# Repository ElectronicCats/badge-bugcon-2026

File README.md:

# Badge BugCON 2026 · Guía de uso

¡Bienvenida, bienvenido a **BugCON 2026**! Esta guía te explica, paso a paso,
cómo usar tu Badge. No necesitas saber de electrónica ni de programación.

## ¿Qué es el Badge?

El Badge es tu gafete electrónico del evento. Diseñado por Electronic Cats
para BugCON 2026, tiene un tema de fútbol: la **Copa BugCon 2026**. Con él
puedes:

- Mostrar tu **estampa**: una tarjeta de jugador con tu apodo, tu villa y tus
  estadísticas.
- **Intercambiar estampas** con otros asistentes y llenar tu **álbum**.
- Jugar **Penales**, la **Copa BugCon** y **Futbolito**.
- Usar herramientas: reloj, temporizador, luz, agenda del evento y control
  remoto para TV.
- Configurarlo desde tu computadora con el [configurador web](#configurador-web):
  una página para tu estampa, tu avatar, tus imágenes y tu álbum.
- Ir más allá con las [herramientas de computadora](tools/README.md).

## Contenido

- [Badge BugCON 2026 · Guía de uso](#badge-bugcon-2026--guía-de-uso)
  - [¿Qué es el Badge?](#qué-es-el-badge)
  - [Contenido](#contenido)
  - [Conoce tu Badge](#conoce-tu-badge)
  - [Encender y apagar](#encender-y-apagar)
    - [Encender](#encender)
    - [Apagar](#apagar)
    - [Reposo automático](#reposo-automático)
  - [Tu primer encendido](#tu-primer-encendido)
  - [Cómo moverte por el Badge](#cómo-moverte-por-el-badge)
  - [El gafete: la pantalla principal](#el-gafete-la-pantalla-principal)
    - [La barra de arriba](#la-barra-de-arriba)
  - [El menú](#el-menú)
  - [Mi Estampa: personaliza tu tarjeta](#mi-estampa-personaliza-tu-tarjeta)
    - [Nickname (tu apodo)](#nickname-tu-apodo)
    - [Villa](#villa)
    - [Posición](#posición)
    - [Estadísticas](#estadísticas)
    - [Desde el teléfono](#desde-el-teléfono)
  - [Intercambiar estampas](#intercambiar-estampas)
    - [Paso a paso](#paso-a-paso)
    - [Qué significa cada resultado](#qué-significa-cada-resultado)
    - [Recibir sin presionar nada](#recibir-sin-presionar-nada)
    - [Visitar las villas](#visitar-las-villas)
    - [Tu privacidad](#tu-privacidad)
  - [El Álbum](#el-álbum)
    - [La portada](#la-portada)
    - [Las páginas](#las-páginas)
    - [Estampas especiales](#estampas-especiales)
  - [Juegos](#juegos)
    - [Penales](#penales)
    - [Copa BugCon](#copa-bugcon)
    - [Futbolito](#futbolito)
  - [Luces](#luces)
  - [Herramientas](#herramientas)
    - [Reloj](#reloj)
    - [Marco](#marco)
    - [Luz ambiental](#luz-ambiental)
    - [Temporizador](#temporizador)
    - [Tokens de IA y SDR](#tokens-de-ia-y-sdr)
  - [TV-Gone y Control remoto](#tv-gone-y-control-remoto)
    - [TV-Gone](#tv-gone)
    - [Control remoto](#control-remoto)
  - [Agenda](#agenda)
  - [Retos y secretos](#retos-y-secretos)
  - [Ajustes](#ajustes)
    - [Para borrar con seguridad](#para-borrar-con-seguridad)
  - [Al cierre del evento: tu estampa de campeón](#al-cierre-del-evento-tu-estampa-de-campeón)
  - [Pilas y energía](#pilas-y-energía)
  - [Qué significan las luces](#qué-significan-las-luces)
  - [Si algo no funciona](#si-algo-no-funciona)
  - [Configurador web](#configurador-web)
    - [Qué necesitas](#qué-necesitas)
    - [Cómo abrirlo](#cómo-abrirlo)
    - [Conectar tu Badge](#conectar-tu-badge)
    - [Pestaña "Plantilla Copa BugCon": tu estampa y tu avatar](#pestaña-plantilla-copa-bugcon-tu-estampa-y-tu-avatar)
    - [Pestaña "Pantalla completa": una imagen en todo el panel](#pestaña-pantalla-completa-una-imagen-en-todo-el-panel)
      - [Usar la imagen como pantalla de inicio](#usar-la-imagen-como-pantalla-de-inicio)
    - [Privacidad](#privacidad)
    - [Si algo no funciona en el configurador](#si-algo-no-funciona-en-el-configurador)
  - [Desde tu computadora](#desde-tu-computadora)
  - [Palabras que conviene conocer](#palabras-que-conviene-conocer)
  - [Créditos y licencia](#créditos-y-licencia)

---

## Conoce tu Badge

| Parte | Para qué sirve |
|---|---|
| **Pantalla** | Muestra todo en blanco y negro. Es de **tinta electrónica**: conserva la imagen aunque el Badge esté apagado, como una hoja impresa. |
| **Flechas** (arriba, abajo, izquierda, derecha) | Mueven la selección. |
| **Botón A** | Acepta o abre lo que elegiste. |
| **Botón B** | Regresa o cancela. |
| **6 luces de colores** | Responden a tus botones y te avisan de lo que pasa. |
| **Interruptor SW1** | Enciende y apaga el Badge. |
| **Portapilas** | Lleva 3 pilas AAA. |
| **Puerto USB-C** | Conecta el Badge a una computadora o a un cargador de celular. |
| **Punta de arriba** | Ahí está el **infrarrojo**: una luz invisible, como la de un control de TV. Sirve para intercambiar estampas y controlar televisores. |
| **Botones RESET y BOOT** | Son pequeños. **RESET** reinicia el Badge sin borrar nada. **BOOT** no lo necesitas para el uso diario. |

> **Un detalle de la pantalla:** cada cambio tarda menos de un segundo y a
> veces parpadea. Es normal en la tinta electrónica.

## Encender y apagar

### Encender

1. Revisa que tenga 3 pilas AAA.
2. Mueve el interruptor **SW1** a la posición de encendido.
3. Verás la copa y el texto "Copa BugCon 2026 · CDMX · 24-27 nov". Las luces
   hacen una ola verde, blanca y roja.
4. Después de unos segundos aparece tu gafete.

### Apagar

- Mueve el interruptor **SW1** a la posición de apagado.
- La pantalla se queda con tu gafete, sin gastar pilas.
- Al apagarlo, el Badge olvida la hora. Tus estampas, tu álbum y tus récords
  **no se borran**.

### Reposo automático

No tienes que apagarlo a cada rato. Si no lo tocas, el Badge ahorra energía
solo:

- Al minuto sin tocar botones, regresa a tu gafete.
- Después de un rato, se duerme. La pantalla sigue mostrando tu gafete.
- Para despertarlo, presiona cualquier botón o muévelo. Una luz destella al
  despertar.

## Tu primer encendido

1. Después de la bienvenida aparece tu gafete. Presiona el botón que
   quieras.
2. Con ese primer botón ganas tu primera estampa especial: **"Debut"**. Las luces festejan.
   Presiona **A** para continuar.
3. El Badge pregunta **"¿Personalizas tu estampa?"** y te muestra tu tarjeta.
   - **A (Sí):** eliges tu apodo, tu villa y más.
     Ve a [Mi Estampa](#mi-estampa-personaliza-tu-tarjeta).
   - **B (Después):** lo haces más tarde desde el menú.

> Mientras no cambies tu apodo, tu estampa dice "Jugador" y cuatro caracteres,
> por ejemplo "Jugador 3F2A", y **no puedes intercambiar estampas**: ponle tu
> nombre primero.

## Cómo moverte por el Badge

| Acción | Qué hace |
|---|---|
| **Flechas** | Mueven la selección. Al llegar al final de una lista, dan la vuelta. |
| **A** | Abre o acepta. |
| **B** | Regresa a la pantalla anterior. |
| **Mantener B** (casi un segundo) | Regresa directo a tu gafete, desde cualquier pantalla. |
| **A + B al mismo tiempo** (en el gafete) | Atajo para intercambiar tu estampa. |

Ayudas que verás siempre:

- **Al pie de la pantalla** se indica qué hacen A y B en ese momento, por
  ejemplo "A Abrir · B Atrás". Si una tecla no aparece, no hace nada ahí.
- **Cada botón enciende una luz** al presionarlo: blanca con las flechas,
  verde con A y roja con B. Así sabes que el Badge te escuchó, aunque la
  pantalla tarde un instante en cambiar.
- **Si algo no se puede hacer**, las luces parpadean tres veces en rojo y la
  pantalla dice por qué.

## El gafete: la pantalla principal

Es lo que el Badge muestra casi siempre, y lo que se queda en la pantalla al
apagarlo. Funciona como tu gafete del evento:

- **Arriba:** una franja negra con tu villa (o "Copa BugCon 2026" si aún no
  eliges una).
- **Al centro:** tu estampa, con tu apodo en letras grandes, tu imagen (si
  subiste una), tu posición y tus estadísticas.
- **Abajo:** "A: menú" y tu número de jugador (por ejemplo, #127). Este
  número se llama **dorsal**: es único para tu Badge. Si tienes imágenes en
  los slots, a la izquierda dice qué se ve: `<Plantilla>` o `<Slot 2>`.

Si cargaste una imagen como pantalla de inicio con el
[configurador web](#configurador-web), ésta ocupa todo el panel, con la franja
de arriba y el pie encima. Vuelves al gafete con **izquierda / derecha** o en
**Ajustes › Pantalla de inicio › Plantilla**. Al cierre del evento, la estampa
de campeón la reemplaza.

Desde el gafete:

- **A** abre el menú.
- **Arriba o abajo** abre las [Luces](#luces).
- **Izquierda o derecha** pasan entre tu gafete y las imágenes de tus slots;
  la que dejes queda como pantalla de inicio. Si no tienes imágenes, el Badge
  te explica cómo subirlas.
- **A + B** inicia un intercambio de estampas.

### La barra de arriba

En casi todas las pantallas, salvo el gafete y los juegos, hay una barra
superior con:

- **La hora.** Si dice `--:--`, el Badge aún no tiene la hora. La forma más
  fácil de ponérsela es conectarlo al [configurador web](#configurador-web):
  la toma de tu computadora al conectar. También puedes pedirla en la mesa de
  soporte o [ponerla con las herramientas](tools/README.md#poner-la-hora).
- **"IR"**, cuando tu Badge está listo para recibir estampas.
- **Una pila** que muestra cuánta energía queda. Es un cálculo aproximado.

## El menú

Presiona **A** en el gafete. El menú tiene 9 secciones en una cuadrícula de
3 × 3. Muévete con las flechas; arriba se lee el nombre de la sección.
Presiona **A** para abrirla.

| Sección | Para qué sirve |
|---|---|
| **Mi Estampa** | Ver y editar tu tarjeta de jugador. |
| **Álbum** | Ver las estampas que juntaste. |
| **Infrarrojo** | Intercambiar estampas, TV-Gone y control remoto. |
| **Juegos** | Penales, Copa BugCon y Futbolito. |
| **Herramientas** | Reloj, marco de imágenes, temporizador, luz, tokens de IA y SDR. |
| **Retos** | Desafíos para personas con experiencia en seguridad. |
| **Ajustes** | Pilas, brillo de luces, ayuda y borrado de datos. |
| **Agenda** | El programa de charlas de BugCON 2026. |
| **Acerca de** | Datos del Badge, su versión y la dirección del [configurador web](#configurador-web). |

El menú recuerda la última sección que abriste.

## Mi Estampa: personaliza tu tarjeta

Tu estampa es lo que ven los demás cuando intercambian contigo.

**Menú › Mi Estampa** muestra tu tarjeta. Presiona **A (Editar)** para
cambiarla. Verás estas opciones y, al pie, la dirección del
[configurador web](#configurador-web), por si prefieres editarla desde una
computadora:

### Nickname (tu apodo)

1. Elige **Nickname**. Aparece un teclado en la pantalla.
2. Muévete con las flechas y presiona **A** para escribir cada letra.
3. Teclas especiales:
   - **Aa**: mayúsculas y minúsculas.
   - **123**: números y símbolos.
   - **«**: borra una letra. Si mantienes A sobre ella, borra todo.
   - **OK**: guarda tu apodo.
4. **B** sale sin guardar.

Caben hasta 16 letras. Las letras con acento y la ñ ocupan el lugar de dos.
Si te pasas, el Badge dice "Ya no caben más letras".

### Villa

Elige tu villa de la lista. La actual tiene una marca `*`. Presiona **A**
para guardar. Villas disponibles: La villa del Hardware, RF Village MX,
Rookie Village, OT Village CDMX, PaySec LATAM, BugBounty, WoSEC México, APT,
Nación Hacker y Live Hacking Villa. Al final de la lista está **Ninguna**.

### Posición

Elige tu posición en la cancha: Portero, Defensa, Medio, Delantero o
Pentester. Presiona **A** para guardar.

### Estadísticas

Tu jugador tiene cuatro estadísticas: **ATK** (ataque), **DEF** (defensa),
**HAX** (hack) y **SUE** (suerte).

- **Arriba / Abajo:** eliges una estadística.
- **Izquierda / Derecha:** restas o sumas 1 punto. Si mantienes el botón,
  cambian de 10 en 10.
- Cada una va de 0 a 99. Tienes 200 puntos para repartir. Arriba ves cuántos
  te quedan libres.
- **A** guarda. **B** cancela.

Tus estadísticas cuentan en la [Copa BugCon](#copa-bugcon).

### Desde el teléfono

Si prefieres escribir en tu celular:

1. Elige **Desde el teléfono**. El Badge enciende su propia red Wi-Fi y
   muestra un código QR.
2. Escanea el QR con la cámara de tu celular. Te conecta a la red del Badge.
3. La página de tu estampa se abre sola. Si no, abre en el navegador la
   dirección que muestra el Badge: `4.3.2.1`.
4. Cambia tus datos y toca **"Guardar en el badge"**.
5. El Badge dice **"¡Guardada!"** y las luces festejan.

Cosas que conviene saber:

- La red del Badge **no tiene Internet**. Tus datos no salen a ningún lado.
- Solo se puede conectar un teléfono a la vez. La contraseña cambia cada vez.
- El Badge muestra cuánto tiempo queda ("Quedan 2:50"). Si no usas la página
  por unos minutos, la red se apaga sola.
- En la página también puedes agregar tu **handle** (tu usuario de redes
  sociales). Solo se comparte si marcas la casilla.
- Si las pilas están casi agotadas, el Wi-Fi no enciende. Cambia las pilas o
  conecta el cable USB.

> También puedes cambiar tu estampa y ponerle una imagen desde una
> computadora. Consulta
> [Personalizar tu estampa](tools/README.md#personalizar-tu-estampa) en la
> guía de herramientas.

## Intercambiar estampas

Cuando intercambias, tu estampa se copia en el álbum de la otra persona y la
suya en el tuyo. Ambos ganan. Se hace con **infrarrojo**, así que los Badges
deben estar muy cerca.

### Paso a paso

1. Acércate a otra persona con Badge.
2. **Junten las puntas de arriba** de los dos Badges, una frente a la otra.
3. Los dos presionan **A + B al mismo tiempo** en su gafete.
   (También pueden ir a **Menú › Infrarrojo › Enviar mi estampa**, o uno
   elige **Enviar mi estampa** y el otro **Recibir**).
4. La pantalla dice **"Buscando..."** y las luces hacen un punto que va y
   viene.
5. Cuando se encuentran, dice **"Intercambiando..."**. **No muevan los
   Badges.** Tarda un par de segundos. Si alguno tiene un avatar que el otro
   aún no tiene, la pantalla dice **"Pasando avatares..."**: tarda unos 8
   segundos si va en un solo sentido y unos 12 si va en los dos (nunca más de
   30). Sigan sin separarlos; las luces se van llenando.
6. Las luces festejan y aparece la estampa que recibiste, con el apodo y el
   avatar de la otra persona.

> **Primero tu nombre:** si aún no cambias tu apodo, en lugar de intercambiar
> el Badge dice **"Primero ponle tu nombre"**. **A (Editar)** abre el editor
> y **B (Atrás)** regresa. No se puede intercambiar con el apodo
> "Jugador XXXX".

### Qué significa cada resultado

| Mensaje | Qué pasó | Qué hacer |
|---|---|---|
| **¡Nueva! 25/400** | Estampa nueva. El número es tu avance en el álbum. | ¡Sigue juntando! |
| **Ya la tenías** | Ya tenías a esa persona. Si cambió algo, se actualiza. | Busca a alguien más. |
| **Avatar incompleto** | La estampa sí se guardó, pero su avatar no terminó de llegar. | Junten las puntas e intercambien otra vez. |
| **No se encontró otro badge** | Nadie respondió. | Pídele a la otra persona que presione A+B. Junten más las puntas. |
| **Se perdió la conexión** | Se movieron o se separaron. | Junten más las puntas y presionen **A (Reintentar)**. |
| **Álbum lleno** | Ya no caben más estampas. | — |
| **No se guardó** | La estampa llegó con un problema. | Intenten de nuevo. |
| **Estampa rechazada** | Uno de los dos Badges no aceptó la estampa del otro. | Intenten de nuevo; si se repite, acérquense a la mesa de soporte. |

Si nadie aparece en unos 20 segundos, el Badge deja de buscar. **B** cancela
la búsqueda en cualquier momento.

### Visitar las villas

Cada una de las 10 villas tiene un **Badge maestro**. Para visitar una villa,
intercambia con su Badge maestro como con cualquier persona:

- La pantalla dice **"¡Nueva! 3/10"** (las villas que llevas) o **"Ya tenías
  esta villa"**, y muestra el nombre y el logo de la villa.
- La visita queda en **Álbum › Villas**.
- Al visitar las 10 ganas la estampa especial **"Gira de villas"** y se abre
  el **Reto de villas** en [Retos](#retos-y-secretos).

### Recibir sin presionar nada

En **Menú › Infrarrojo › Activar recepción**, tu Badge queda listo para
recibir estampas durante 10 minutos, aunque no estés tocando los botones. La
barra de arriba muestra **"IR"** mientras está activa. La opción cambia a
**Apagar recepción** para desactivarla antes.

### Tu privacidad

Al intercambiar, la otra persona recibe tu apodo, villa, posición,
estadísticas y dorsal. Tu handle solo va si lo autorizaste. Tu **avatar**
también va (reducido a 64 × 64), salvo que lo apagues en **Menú › Mi Estampa ›
Editar › Compartir avatar**; en ese caso tú sí recibes el de la otra persona.
Una vez que la estampa o el avatar están en otro Badge, no se pueden retirar.

## El Álbum

**Menú › Álbum** muestra cuántas estampas tienes, por ejemplo
**"Álbum 25/400"**. Tu propia estampa ya cuenta.

### La portada

Es una lista con secciones:

- **Última:** la estampa más reciente que recibiste.
- **Todas:** un lugar para cada uno de los 400 Badges del evento.
- **Una sección por villa**, con cuántas tienes de cada una. Si alguien no
  eligió villa, su estampa va en **Sin villa**.
- **Especiales:** las estampas que ganas por logros.
- **Villas:** las 10 villas del evento y cuáles ya
  [visitaste](#visitar-las-villas) ("Sí"). En una visitada, **A (Ver)**
  muestra el pedazo que te dio su villa: lo vas a necesitar.

### Las páginas

- En **Todas**, cada lugar tiene su número. Un borde punteado indica un lugar
  vacío. Un borde completo indica una estampa que ya tienes. El tuyo dice
  **"Tú"**.
- Muévete con las flechas. Si mantienes izquierda o derecha, pasas de página.
- **A (Ver)** abre la estampa. Ahí, izquierda y derecha pasan a la anterior
  o a la siguiente.
- Si una sección está vacía, **A (Intercambiar)** te lleva directo a buscar
  otro Badge.

### Estampas especiales

Algunos logros te dan una estampa especial. Cuando ganas una, aparece
**"¡Estampa especial!"** sobre cualquier pantalla y las luces festejan.
Presiona **A** para cerrarla. Algunos ejemplos:

| Estampa | Cómo se gana |
|---|---|
| Debut | Presionar tu primer botón. |
| Primer pase | Tu primer intercambio. |
| Convocado | Juntar 10 estampas. |
| Titular | Juntar 50 estampas. |
| Capitán | Juntar 100 estampas. |
| Guante de Oro | Atajar 3 penales en una misma tanda. |
| Gira de villas | [Visitar las 10 villas](#visitar-las-villas). |

Hay más estampas escondidas. ¡Explora tu Badge para encontrarlas!

## Juegos

**Menú › Juegos** tiene tres juegos. Elige con **arriba / abajo** y presiona
**A (Jugar)**. En cualquier juego, **B** sale.

### Penales

Tú contra la **CPU** (el propio Badge, que juega como rival). Cada lado tira
5 penales. Si empatan, siguen tirando hasta que uno falle.

**Cuando tiras:**

1. Apunta con las flechas a una de las 6 zonas de la portería.
2. **Mantén A.** Las luces se van encendiendo: es la fuerza del tiro.
3. **Suelta A antes de que se encienda la última luz.** Si se encienden
   todas, el balón se va afuera.

**Cuando atajas:**

1. Elige un lado con **izquierda o derecha**, o quédate al centro.
2. Presiona **A** para lanzarte.

Al final ves si ganaste, tus atajadas y tus récords. **A (Otra vez)** juega
de nuevo. Consejo: la CPU aprende hacia dónde tiras. ¡Cambia de lado!

### Copa BugCon

Un partido por turnos con tu propio equipo. Tu equipo se forma con tu estampa
y con las estampas de tu álbum: **cada estampa que intercambias es un
fichaje**.

1. **Arma tu plantilla.** Hay 5 lugares, uno por posición. Con **arriba /
   abajo** eliges un lugar y con **izquierda / derecha** cambias quién juega
   ahí. Si te faltan estampas, entra un "Suplente".
2. Presiona **A (Jugar)**.
3. En cada jugada, tú y la CPU eligen una táctica al mismo tiempo, sin
   verse. Elige con **arriba / abajo** y confirma con **A**.
4. El partido tiene 2 tiempos de 6 jugadas cada uno.

Las tácticas funcionan como piedra, papel o tijera:

| Táctica | Le gana a |
|---|---|
| **Atacar** | Parche de seguridad |
| **Presionar** | Contragolpe |
| **Contragolpe** | Atacar |
| **Parche de seguridad** | Presionar (además, protege el balón) |

Si repites siempre la misma táctica, la CPU aprende a contestarla.

- La primera vez, un tutorial corto te enseña a jugar. Puedes repetirlo con
  **"¿Cómo se juega?"** en la plantilla.
- **Copa con otro badge:** juega contra un amigo. Uno elige **Buscar** y el
  otro **Esperar**. Junten las puntas de arriba de los Badges.

### Futbolito

Un futbolito de mesa visto desde arriba. Tus muñecos son los negros; los de
la CPU, los blancos. Gana quien meta 3 goles, o quien lleve más al acabarse
el tiempo.

1. Pon el Badge **sobre una mesa, con la pantalla hacia arriba**, y déjalo
   quieto un segundo. El partido empieza solo.
2. **Inclina el Badge** a los lados para mover tus barras. Las luces muestran
   dónde están.
3. **Da un golpecito en la mesa**, junto al Badge, para patear.
4. **Levanta el Badge** para pausar. Ponlo de nuevo en la mesa para seguir.

¿No tienes mesa? Presiona **A** en la primera pantalla para jugar con
botones: izquierda y derecha mueven las barras y A patea.

La primera vez, un tutorial con tres retos te enseña a jugar. Para repetirlo,
presiona **arriba** en la pantalla "Pon el badge sobre la mesa".

## Luces

Desde el gafete, presiona **arriba o abajo** para abrir las Luces.

| Acción | Qué pasa |
|---|---|
| **Flechas** | Las 6 luces toman el color de una villa y la pantalla muestra su nombre. La primera vez se enciende el color de tu villa. |
| **A** | Ola de estadio en verde, blanco y rojo. |
| **B** | Apaga las luces. |
| **Sacudir el Badge** | ¡Porra! Las luces festejan como en un gol. |
| **Mantener B** | Regresa a tu gafete. |

## Herramientas

**Menú › Herramientas** tiene varias vistas. Cámbialas con **izquierda /
derecha**; arriba se lee cuál ves, por ejemplo "< Reloj 1/5 >". **B** sale.

### Reloj

Muestra la hora y la fecha en grande. Si el Badge no tiene la hora, conéctalo
al [configurador web](#configurador-web) o pídela en la mesa de soporte.

### Marco

Muestra a pantalla completa una imagen guardada en tu Badge. Con **arriba /
abajo** cambias de imagen. Caben 4 imágenes. Se cargan desde una computadora
con el [configurador web](#configurador-web) (pestaña **Pantalla completa**) o
con las [herramientas de computadora](tools/README.md#imágenes-para-el-marco).
Si necesitas ayuda, acércate a la mesa de soporte.

### Luz ambiental

En el Reloj y en el Marco, cada vez que presionas **A** cambia la luz:
apagada → cálida → blanca → ola. Así tu Badge sirve como lámpara de escritorio.

### Temporizador

1. Elige los minutos con **arriba / abajo** (de 1 a 99).
2. Presiona **A (Iniciar)**. Las luces muestran el tiempo que queda.
3. Al terminar, la pantalla dice **"¡Tiempo!"** y las luces hacen una ola.
   Presiona cualquier botón para callar el aviso.

**A (Parar)** detiene el temporizador antes de tiempo.

### Tokens de IA y SDR

Son funciones avanzadas que solo trabajan con el Badge conectado por USB a una
computadora con su programa. Sin computadora, el Badge te lo indica en
pantalla. Para los Tokens, consulta
[El Badge en tu escritorio](tools/README.md#el-badge-en-tu-escritorio).
La vista **SDR** muestra la dirección de su visor web,
`espargos.net/espsdr/app/`, que se abre en la computadora.

> Mientras el temporizador corre, o si el Badge está conectado por USB,
> Herramientas no regresa sola al gafete.

## TV-Gone y Control remoto

Los dos están en **Menú › Infrarrojo**. Apunta siempre con la **punta de
arriba** del Badge y **de cerca** (empieza a menos de un metro).

### TV-Gone

Envía los códigos de apagado de las marcas de TV más comunes, uno tras otro.

1. La primera vez aparece un aviso de **uso responsable**. Úsalo solo con
   televisores tuyos o con permiso de su dueño. **No apagues las pantallas
   del evento.** Presiona **A (Acepto)**.
2. Elige la región con **izquierda / derecha**: América, Europa o Todas. Si
   no sabes dónde se compró la TV, elige **Todas**.
3. Apunta a la TV y presiona **A**. Las luces llenan una barra. No muevas el
   Badge hasta que diga **"Listo"**.

Si la TV ya estaba apagada, puede encenderse. En ese caso, repite.

### Control remoto

Tu Badge puede copiar los botones de tus controles (TV, bocina, proyector…) y
repetirlos.

1. Abre **Control remoto** y elige una marca (ya vienen 12 marcas de TV) o
   crea la tuya con **"+ Agregar marca"**.
2. Elige un botón, por ejemplo "Encender", y presiona **A (Aprender)**.
3. Pon tu control a unos centímetros de la punta de arriba del Badge y
   presiona **una vez** el botón que quieres copiar.
4. Cuando diga **"Código leído"**, presiona **A (Guardar)**.
5. Para usarlo, elige el botón y presiona **A**. Si mantienes A, se repite,
   como al subir el volumen.

¿Tienes controles guardados de un Flipper Zero? Puedes cargarlos desde tu
computadora: consulta
[Control remoto: archivos de Flipper Zero](tools/README.md#control-remoto-archivos-de-flipper-zero).

## Agenda

**Menú › Agenda** muestra el programa de charlas de BugCON 2026.

- Muévete con **arriba / abajo** y presiona **A (Ver)** para ver los detalles
  de una charla.
- Si el Badge tiene la hora, marca la charla **"En curso"** o la
  **"Próxima"**.
- Si dice "El badge no tiene la hora", el pie te da la dirección del
  [configurador web](#configurador-web)
  (`electroniccats.github.io/badge-bugcon-2026/configurator`): conéctalo por
  USB y la hora se pone sola. También puedes pedirla en la mesa de soporte.

## Retos y secretos

- **Retos:** son desafíos para personas con experiencia en seguridad
  informática. La sección te dice por dónde empezar: **"Acerca de"**. Cada
  etapa que superes te da una estampa de reto. Para entregar la respuesta (la
  **flag**, una clave secreta) se necesita una computadora: consulta
  [Entregar la flag de un reto](tools/README.md#entregar-la-flag-de-un-reto).
- **Reto de villas:** aparte de las etapas, se abre al
  [visitar las 10 villas](#visitar-las-villas). Mientras tanto, la sección
  dice cuántas llevas. Guarda los pedazos que te dan las villas
  (**Álbum › Villas**): los vas a necesitar.
- **Secretos:** el Badge esconde algunas sorpresas que dan estampas
  especiales. Una pista: prueba combinaciones de botones famosas y observa qué
  hace el Badge en posiciones poco comunes.

## Ajustes

**Menú › Ajustes** tiene estas opciones:

| Opción | Qué hace |
|---|---|
| **Pilas nuevas** | Úsala cada vez que cambies las pilas. Pone el indicador de pilas en lleno. No borra nada. |
| **Brillo de LEDs** | Cambia qué tan fuerte brillan las luces, con **izquierda / derecha** (5 niveles). Las luces se encienden en blanco para que veas cómo queda. **B (Listo)** guarda. |
| **Pantalla de inicio** | Elige qué ves en reposo: la **Plantilla** (tu gafete) o uno de los slots que llenaste con el [configurador web](#configurador-web) ("Slot n"). La actual dice "activa". |
| **Cómo usar** | Una ayuda rápida de 3 pantallas. |
| **Borrar progreso** | Borra tus récords de juegos, todas las estampas de tu álbum (también las especiales y las de retos), los tiros de los retos que recibiste y tu estampa de campeón. Tu estampa se conserva. |
| **Borrar datos** | Borra todo lo anterior y también tu estampa, tu apodo, tu avatar, tus marcas y botones del control remoto, los tutoriales vistos, el aviso de TV-Gone, el brillo de las luces y las imágenes de los 4 slots. La pantalla de inicio vuelve a ser tu gafete. El Badge queda como nuevo. |

### Para borrar con seguridad

Borrar **no se puede deshacer**, así que el Badge pide confirmación:

1. Elige la opción y presiona **A**. Verás qué se va a borrar y las luces
   parpadearán en rojo.
2. **Mantén A presionado** para borrar. Un toque corto no borra.
3. Si cambias de opinión, presiona **B (Cancelar)**.

## Al cierre del evento: tu estampa de campeón

Al terminar BugCON 2026 (viernes 27 de noviembre, 18:00), tu gafete se
convierte en tu **estampa de campeón**.
Muestra una copa, la palabra "Campeón", tu apodo y tu resumen del evento:

- **Álbum:** cuántas estampas juntaste.
- **Especiales:** cuántas estampas especiales ganaste.
- **Retos:** cuántas etapas superaste.
- **Penales:** cuántas tandas ganaste.
- **Atajadas:** tu récord de atajadas en una tanda.

Ocurre solo cuando el Badge tiene la hora, o en la mesa de soporte. Como la
pantalla conserva la imagen, tu resumen se queda ahí como recuerdo, incluso
con el Badge apagado.

## Pilas y energía

- **Pilas:** 3 pilas AAA alcalinas. Con pilas nuevas, el Badge dura alrededor
  de una semana de uso normal. Es una estimación.
- **Indicador:** la pila de la barra superior es un cálculo aproximado, no
  una medición. Por eso, **cada vez que cambies las pilas**, ve a
  **Ajustes › Pilas nuevas**.
- **Cable USB:** mientras está conectado, el Badge usa la energía del cable y
  no gasta pilas. **El cable no recarga las pilas.** El interruptor SW1 debe
  estar encendido.
- **Pilas agotadas:** si las pilas ya no alcanzan, la pantalla dice **"Cambia
  las pilas"** y el Badge se duerme. Cámbialas o conecta el cable USB.
- **Para guardarlo** mucho tiempo, apágalo con SW1 y saca las pilas.

## Qué significan las luces

| Lo que ves | Qué significa |
|---|---|
| Una luz que destella al presionar un botón | El Badge recibió tu botón. Blanca: flecha. Verde: A. Roja: B. |
| Ola verde, blanca y roja | Bienvenida al encender, ola de las Luces o fin del temporizador. |
| Un punto de luz que va y viene | Está buscando otro Badge o intercambiando. |
| Destellos de colores que terminan en verde | ¡Festejo! Intercambio exitoso, estampa especial, gol o algo guardado. |
| Tres parpadeos rojos | Algo no se pudo hacer, perdiste el punto o recibiste un gol. |
| Rojo parpadeando sin parar | Te está pidiendo confirmar un borrado. |
| Luces que se van llenando | Una barra de avance: fuerza del penal, tiempo del temporizador o TV-Gone enviando. |
| Luces de un solo color | Estás en Luces o usando la luz ambiental. |
| Una luz breve al despertar | El Badge salió del reposo. |

## Si algo no funciona

| Problema | Qué hacer |
|---|---|
| La pantalla no cambia al presionar botones | El Badge puede estar dormido: presiona un botón y espera un segundo. Si sigue igual, revisa que SW1 esté encendido y cambia las pilas. |
| El Badge no responde | Presiona **RESET** o apágalo y enciéndelo con SW1. No se borra nada. |
| Aparece una pantalla de pruebas al encender | Encendiste el Badge con A y B presionados. Apágalo y enciéndelo sin presionar botones. |
| La pantalla se quedó congelada justo al encender | Quizá presionaste BOOT al encender. Apágalo y enciéndelo sin presionar botones. |
| No puedo intercambiar | Junten bien las puntas de arriba, no muevan los Badges y que los dos presionen A+B. |
| La hora dice `--:--` | Conecta el Badge al [configurador web](#configurador-web): pone la hora al conectar. También puedes pedirla en la mesa de soporte o [ponerla con las herramientas](tools/README.md#poner-la-hora). Recuerda que se pierde al apagar con SW1. |
| La pila marca vacía pero las pilas son nuevas | Ve a **Ajustes › Pilas nuevas**. |
| Quiero empezar de cero | **Ajustes › Borrar datos** (mantén A para confirmar). |
| Sigues con dudas | Acércate a la mesa de soporte de BugCON 2026. |

## Configurador web

El configurador es una página que se abre en el navegador de tu computadora y
habla con tu Badge por el cable USB. Es la forma más sencilla de personalizar
tu estampa con una imagen, subir imágenes a pantalla completa y guardar tu
álbum. No instalas nada, no hay cuenta y **nada de lo que hagas se envía a
Internet**: todo se queda entre tu computadora y tu Badge.

### Qué necesitas

- Una **computadora** con **Chrome, Edge o Brave** (en Firefox, Safari y
  celulares la página abre, pero no puede conectar el Badge; te lo dice en
  pantalla. Desde el celular usa el Wi-Fi del Badge:
  [Desde el teléfono](#desde-el-teléfono)).
- Un **cable USB-C de datos**. Algunos cables son solo de carga y no sirven.
- Tu Badge **encendido** con SW1.

### Cómo abrirlo

Elige una de estas formas. En todas es la misma página:

| Forma | Pasos |
|---|---|
| **En línea (GitHub Pages)** | Abre <https://electroniccats.github.io/badge-bugcon-2026/configurator/> en tu navegador. |
| **Descargar el .zip** | Baja [bugcon26-configurador.zip](https://github.com/ElectronicCats/badge-bugcon-2026/releases/latest/download/bugcon26-configurador.zip) de la última versión, **extrae todo** (en Windows: clic derecho › *Extraer todo*) y abre `configurator/index.html` con tu navegador. |
| **Clonar el repositorio** | Clónalo y abre `web/configurator/index.html` con tu navegador (clic derecho › *Abrir con*). Si prefieres un servidor local, desde la carpeta `web/` ejecuta `python3 -m http.server 8000` y abre <http://localhost:8000/configurator/>. |

La página es un solo archivo, sin librerías ni servidores externos, así que
también funciona **sin Internet**. Para que el enlace **Ver el álbum**
funcione, la carpeta `album/` debe estar junto a `configurator/`; si abres el
`.html` desde dentro del .zip, no funciona.

> En Linux, si el navegador no puede abrir el puerto, agrega tu usuario al
> grupo `dialout` (`sudo usermod -aG dialout $USER`) y vuelve a iniciar
> sesión. Si conecta pero el Badge "no contestó", ejecuta
> `stty -F /dev/ttyACM0 min 1`.

### Conectar tu Badge

1. Conecta el Badge a la computadora con el cable USB.
2. En la página, presiona **Conectar**.
3. El navegador abre una lista de puertos. Elige **USB JTAG/serial debug
   unit** y acepta.
4. El botón cambia a **Desconectar** y la página le pone al Badge la hora de
   tu computadora y lee tu estampa, tu avatar y qué hay en sus imágenes.

Solo un programa puede usar el Badge a la vez. Si la página dice que el
puerto está ocupado, cierra otras pestañas del configurador, el monitor
serie de Arduino o las [herramientas de computadora](tools/README.md).
Mientras la página está abierta y conectada, esos programas no pueden usar el
Badge.

Aunque no tengas el Badge a la mano, **sí puedes preparar una imagen** y ver
cómo quedaría; solo no podrás enviarla.

La página tiene **dos pestañas**: la **Plantilla Copa BugCon**, que se abre
por defecto, y **Pantalla completa**. Cambias con un clic o con las flechas
← → (también Inicio y Fin) del teclado. Cada pestaña numera sus pasos: sigue
el orden de las tarjetas. Los textos largos están en **Más información**.
Arriba, junto a **Conectar**, el enlace **Ver el álbum** abre la página del
álbum.

### Pestaña "Plantilla Copa BugCon": tu estampa y tu avatar

Sirve para editar tu estampa, ponerle una imagen (tu **avatar**, de 96 × 96
puntos) y ver tu **plantilla** (tu gafete completo) tal como lo muestra el
Badge.

1. **Mi estampa.** Escribe tu **Nickname** (hasta 16 bytes; la ñ y los acentos
   ocupan dos), elige tu **Villa** y tu **Posición** y reparte tus
   **Estadísticas** (200 puntos en total; arriba ves cuántos te quedan). Si
   quieres, marca **Compartir mi handle** y escríbelo.
   - **Leer mi estampa del badge** trae la estampa que ya tienes en el Badge.
   - **Guardar estampa** la guarda en el Badge; el Badge la firma y la página
     muestra "Estampa guardada y firmada por el badge". Junto a los botones
     ves si está **Guardada en el badge** o **Sin guardar**.
2. **Imagen.** Arrastra una imagen a la página, pégala del portapapeles o usa
   **Abrir archivo** o **Usar la cámara**. Mueve el recuadro para encuadrar y
   cambia su tamaño con el control **Recorte** o la rueda del ratón (con el
   teclado, enfoca la imagen y usa las flechas y +/−). Puedes **Girar imagen
   90°** o **Voltear horizontal / vertical**.
3. **Ajustes y Tramado.** El panel es de blanco y negro, así que la página
   convierte tu imagen con puntitos (tramado). Juega con brillo y contraste;
   gamma, punto negro, punto blanco y nitidez están en **Más ajustes**.
   **Ajustar niveles** los calcula solo, **Invertir colores** cambia blanco
   por negro y **Restablecer ajustes** lo deja como estaba. Puedes agregar
   **Texto encima** y arrastrarlo en la vista previa.
4. **Vista previa.** Lo que ves ahí es exactamente lo que recibe el Badge.
5. **Plantilla.** Muestra tu gafete completo, tal como lo verás en el Badge.
   Se actualiza al guardar la estampa y al enviar el avatar. Presiona
   **Enviar avatar**: la imagen aparece en tu plantilla. Al intercambiar
   estampas, tu avatar también viaja a los otros Badges (reducido a 64 × 64)
   y se guarda en su álbum, salvo que desmarques **Compartir mi avatar por
   infrarrojo** en esta pestaña y guardes la estampa (también puedes hacerlo en
   el Badge: **Mi Estampa › Editar › Compartir avatar**). La plantilla no sale
   de tu Badge.

Más cosas en esta pestaña:

- **Álbum › Guardar álbum (.json)** guarda en tu computadora tu estampa y las de tu
  álbum, con los avatares que recibiste. El archivo incluye el nickname, el
  handle y el avatar que cada quien compartió contigo: **no lo publiques**. Para verlo, usa **Ver el álbum**, presiona
  **Abrir álbum…** y elige el `.json` (o arrástralo a la página). Ahí puedes
  filtrar las que **Tengo** o **Me faltan**, ir directo a un dorsal,
  imprimirlo desde el navegador y descargar los contactos
  (**Descargar contactos (.vcf)**).
  **Abrir el configurador** te regresa.

### Pestaña "Pantalla completa": una imagen en todo el panel

Sirve para preparar una imagen de 200 × 200 que ocupa **todo** el panel, sin
la barra de estado, y guardarla en uno de los 4 **slots** del Badge.

1. Prepara la imagen igual que en la otra pestaña (Imagen, Ajustes, Tramado,
   Texto encima). **Cada pestaña recuerda su propia imagen**: lo que haces
   aquí no cambia tu avatar.
2. Elige el **Encuadre**:
   - **Rellenar (recorta):** llena todo el panel y corta lo que sobra.
   - **Encajar completa:** muestra la imagen entera y deja bandas; en **Bandas** eliges **Blanco**
     o **Negro**. Úsalo con fotos horizontales o verticales.
3. Marca **Mostrar guías** si quieres ver qué tapa el Badge: la línea roja
   marca la franja de abajo, donde aparecen "Luz" y "Salir" al entrar al
   Marco. Es solo una guía; no se envía.
4. Elige el **slot** (0 a 3). Cada uno dice si tiene una **imagen** o está
   **vacío**, y cuál es el de **inicio**.
   - Si tu editor está vacío, al elegir un slot se carga la imagen que tiene.
   - Si ya tienes una imagen en el editor, no se pierde. Para traer la del
     slot a propósito, presiona **Editar la imagen del slot n**.
5. Presiona **Enviar al slot n**. Se guarda y se abre a pantalla completa en
   el Badge. Si el slot ya tenía una imagen, antes te pide confirmar.

En el Badge:

- **B** cierra la imagen. Si no tocas botones, el Badge vuelve solo a su
  pantalla de inicio al minuto. No se borró: sigue en su slot.
- Para verla después: **Menú › Herramientas › Marco** (con **arriba / abajo**
  pasas de una a otra) o el botón **Mostrar slot n** de la tarjeta **En el
  badge**.
- Esa tarjeta también tiene **Pantalla en blanco**, que deja el panel en
  blanco, y **Vaciar slot n**, que borra la imagen del Badge (pide confirmar).
- **Enviar patrón de prueba** manda un borde y una marca en la esquina para
  comprobar que la imagen sale completa y sin cortes; reemplaza la imagen del
  slot, así que también pide confirmar si estaba ocupado.

#### Usar la imagen como pantalla de inicio

Marca **Usar como inicio** antes de enviar y la imagen **reemplaza a tu
plantilla** cuando el Badge está en reposo. Encima se dibujan la franja de
arriba (tu villa) y el pie (pista y dorsal), así que no pongas nada
importante ahí; **Mostrar guías** te los marca.

Para regresar a tu plantilla tienes dos formas:

- En la página, el botón **Volver a la plantilla** (aparece cuando hay un
  inicio activo, en las dos pestañas).
- En el Badge, **izquierda / derecha** en el gafete, o **Menú › Ajustes ›
  Pantalla de inicio › Plantilla**, sin computadora.

La estampa de campeón del cierre del evento siempre tiene prioridad sobre la
imagen de inicio. Si la casilla **Usar como inicio** no aparece, tu Badge
tiene un programa más viejo que no la incluye.

### Privacidad

La página no tiene servidor ni almacenamiento central: tu estampa, tu avatar
y tu álbum se guardan solo en tu Badge, y nadie recibe una copia. Tu handle
solo se comparte si marcas la casilla. Tu avatar sale por infrarrojo a quien
intercambie contigo, salvo que desmarques **Compartir mi avatar por
infrarrojo**; una vez en otro Badge no se puede retirar. Para borrar tu estampa,
tu avatar, tu álbum y las imágenes de los slots, usa **Ajustes › Borrar datos**
en el Badge.

### Si algo no funciona en el configurador

| Problema | Qué hacer |
|---|---|
| El botón **Conectar** está apagado | Tu navegador no tiene Web Serial. Usa Chrome, Edge o Brave de escritorio, actualizado. |
| La lista de puertos sale vacía | Prueba otro cable (debe ser de datos) u otro puerto USB y revisa que el Badge esté encendido. Si la ventana ni aparece, activa el permiso "Puertos serie" en la configuración del sitio del navegador. |
| "No se pudo abrir el puerto" | Algo más está usando el Badge: cierra otras pestañas, el monitor serie o las herramientas de computadora y espera unos segundos. |
| "El badge no contestó" | Desconecta y conecta de nuevo. En Linux, ejecuta `stty -F /dev/ttyACM0 min 1`. |
| Quise enviar y dice "Carga una imagen primero" | Aún no hay imagen en el editor de esa pestaña: arrastra una o usa **Abrir archivo**. |
| Dice "Conexión perdida" | Se salió el cable o el Badge se reinició. Revisa el cable y presiona **Conectar** otra vez. |
| Dice "El badge está ocupado" | Está terminando otra operación (refrescar la pantalla tarda unos segundos). Espera y vuelve a intentar. |
| Mi imagen desapareció del Badge | A los 60 segundos sin botones vuelve al inicio. Ábrela de nuevo con **Mostrar slot n** o en **Marco**. |
| El **Ver el álbum** no abre | Extrae todo el .zip, o abre la página desde el repositorio completo: `album/` debe estar junto a `configurator/`. |

## Desde tu computadora

Si conectas tu Badge a una computadora con un cable USB, puedes hacer más
cosas. Muchas se hacen con el [configurador web](#configurador-web) y todas
con las herramientas de computadora:

- Ponerle la hora.
- Cambiar tu estampa y ponerle una imagen.
- Guardar imágenes para el Marco.
- Guardar una copia de tu álbum.
- Cargar controles remotos de Flipper Zero.
- Usar las luces como aviso en tu escritorio y ver tu consumo de
  inteligencia artificial.
- Entregar la flag de un reto.

La [guía de herramientas de computadora](tools/README.md) te explica, paso a
paso, cómo prepararla y usar cada función.

## Palabras que conviene conocer

| Palabra | Significado |
|---|---|
| **Estampa** | Tu tarjeta de jugador: apodo, villa, posición y estadísticas. |
| **Álbum** | La colección de estampas que recibes de otros asistentes. |
| **Avatar** | La imagen de 96 × 96 puntos de tu estampa. Al intercambiar, los otros Badges reciben una copia de 64 × 64. |
| **Slot** | Cada uno de los 4 espacios del Badge para imágenes a pantalla completa (0 a 3). |
| **Web Serial** | Función de Chrome, Edge y Brave que deja a una página hablar con tu Badge por USB. |
| **Dorsal** | El número único de tu Badge, como el de una playera. |
| **Villa** | Tu comunidad o área de interés en el evento. |
| **Nickname** | Tu apodo. |
| **Handle** | Tu nombre de usuario en redes sociales. |
| **Infrarrojo** | Luz invisible, como la de un control de TV. El Badge la usa para comunicarse. |
| **CPU** | El rival que controla el propio Badge en los juegos. |
| **Tinta electrónica** | Tipo de pantalla que conserva la imagen sin energía. |
| **Flag** | La respuesta secreta de un reto. |

---

## Créditos y licencia

Badge diseñado por [Electronic Cats](https://electroniccats.com) para BugCON
2026. El hardware, las páginas web y las herramientas de este repositorio son
abiertos, bajo la licencia GPL-3.0 ([LICENSE](LICENSE)). Los componentes de
terceros están en [THIRD_PARTY.md](THIRD_PARTY.md).

Electronic Cats invierte tiempo y recursos en este diseño abierto. ¡Apoya a
Electronic Cats y al hardware libre comprando sus productos!

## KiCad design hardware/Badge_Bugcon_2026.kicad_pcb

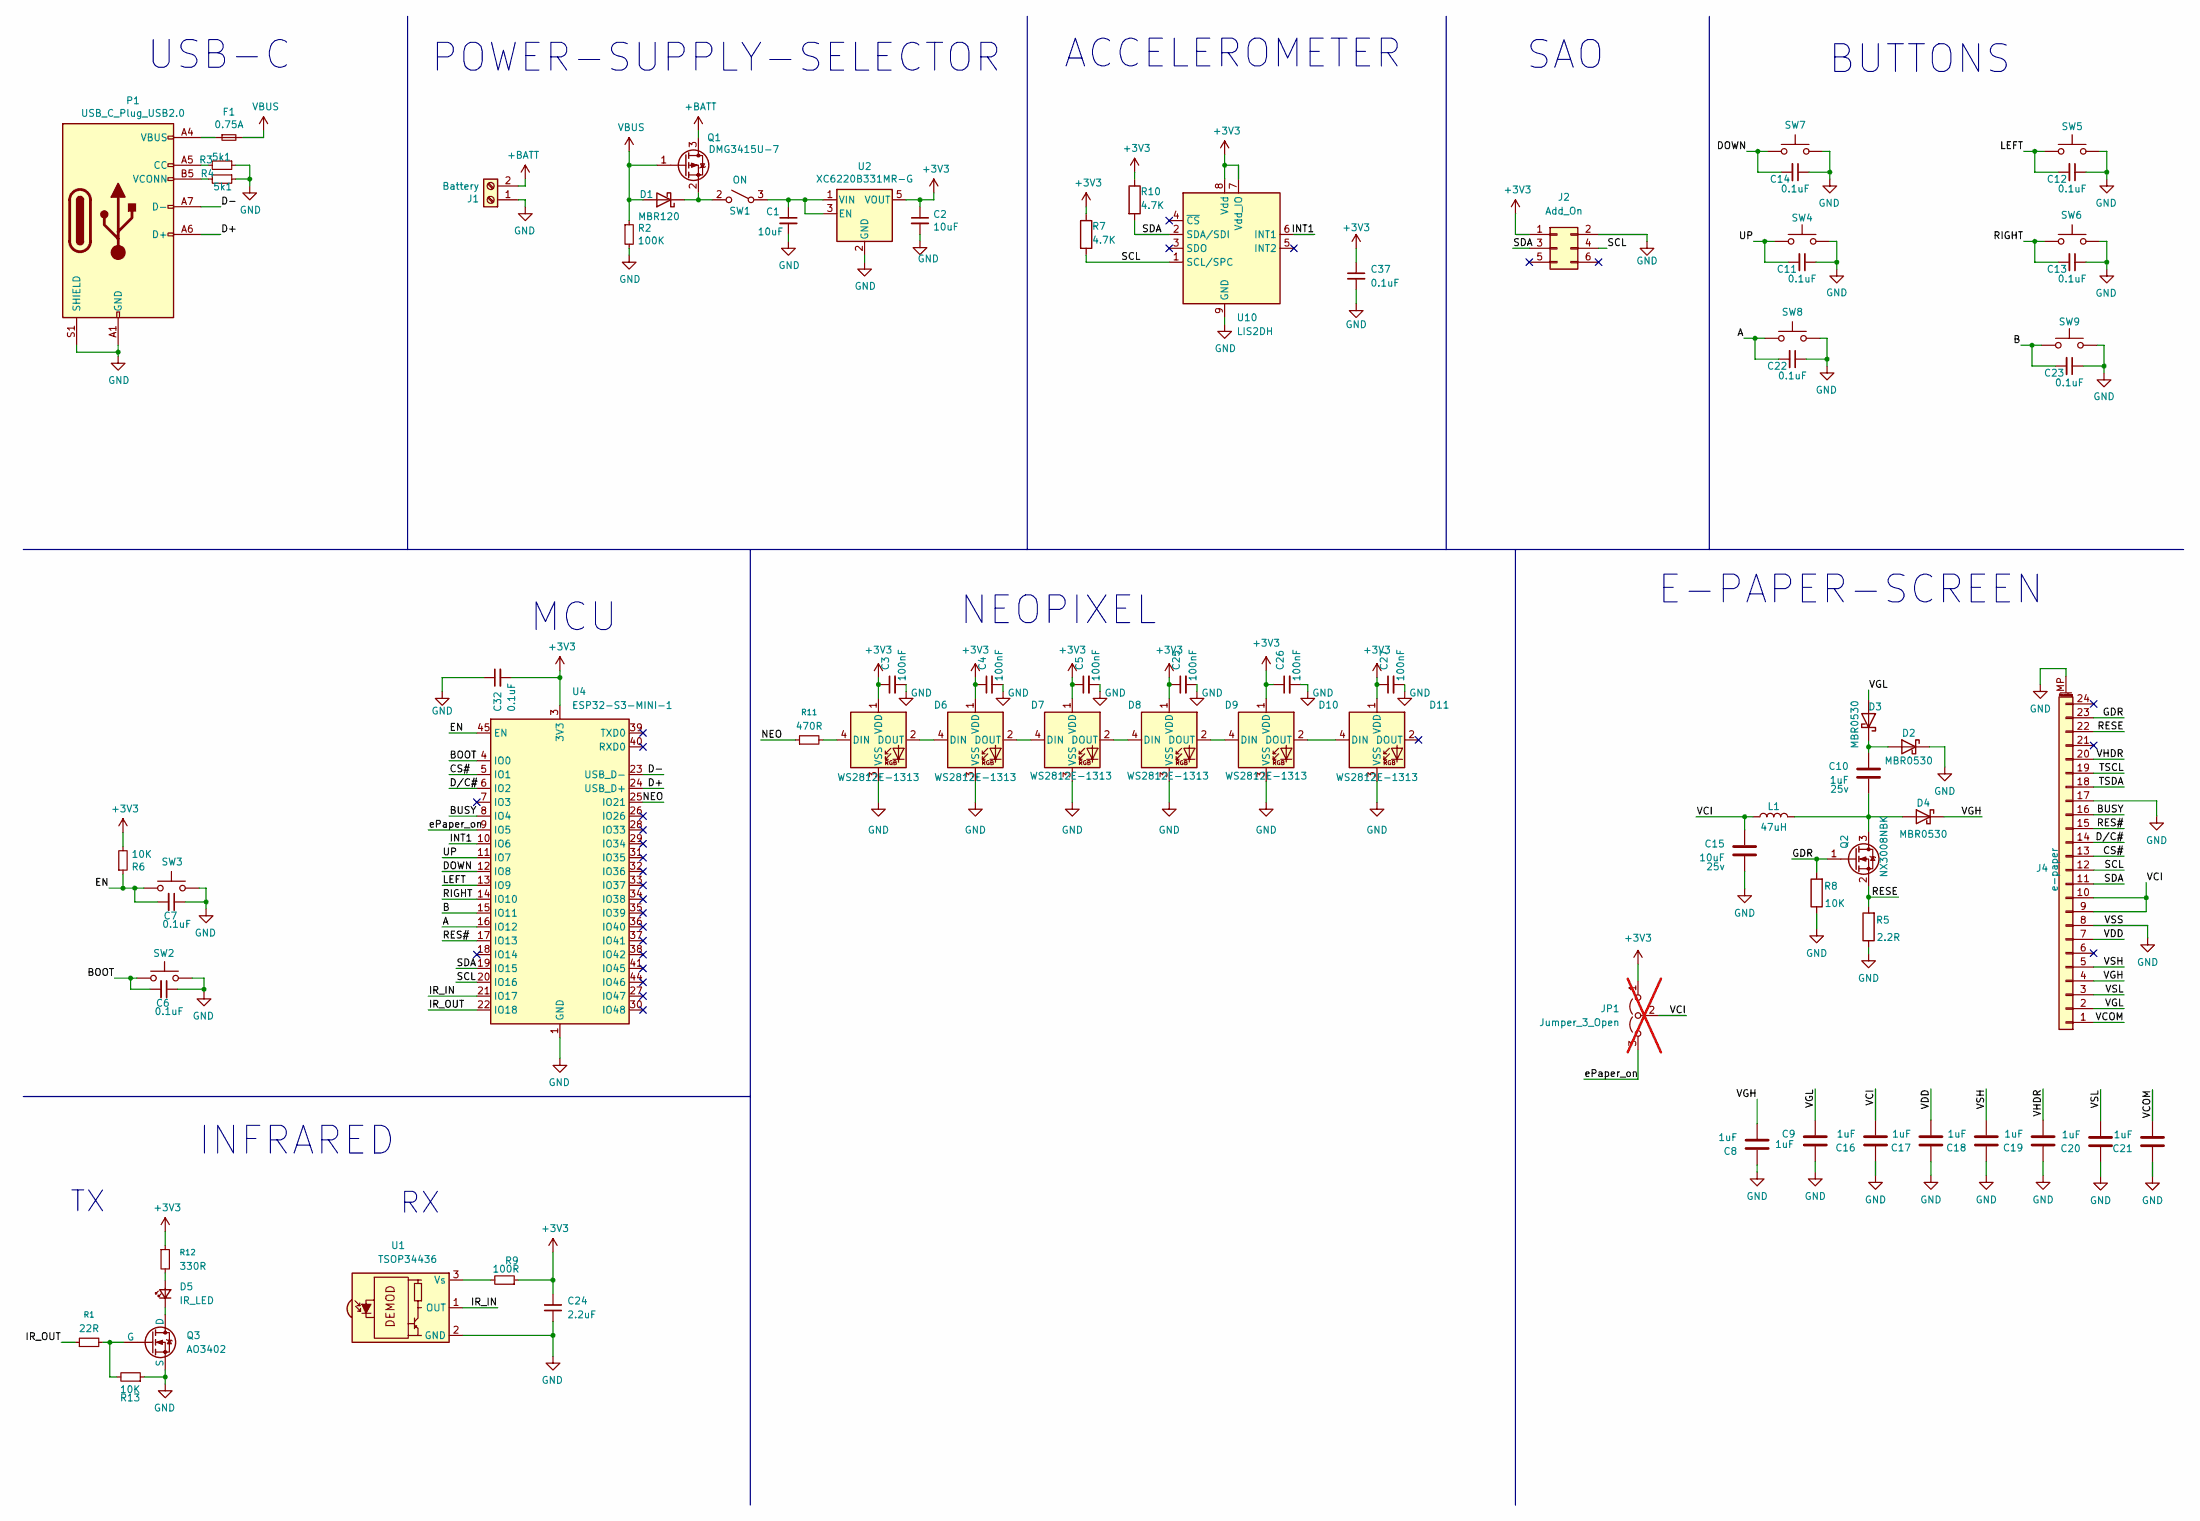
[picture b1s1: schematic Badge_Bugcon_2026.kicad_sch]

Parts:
C1, C2: 10uF; C_0603_1608Metric; LCSC# C7393892
C3, C4, C5, C25, C26, C27: 100nF; C_0603_1608Metric; LCSC C338117
C6, C7, C11, C12, C13, C14, C22, C23, C37: 0.1uF; C_0603_1608Metric; LCSC# C30926
C8, C9, C10, C16, C17, C18, C19, C20, C21: 1uF; C_0603_1608Metric; Voltage 25v; LCSC# C5199872
C15: 10uF; C_0603_1608Metric; Voltage 25v; LCSC# C7393892
C24: 2.2uF; C_0603_1608Metric; LCSC# C23630
C32: 0.1uF; C_0402_1005Metric; LCSC# C2167824
D1: MBR120; D_SOD-123F; LCSC# C896755
D2, D3, D4: MBR0530; D_SOD-123; LCSC# C82046
D5: IR_LED; LED_D3.0mm_Horizontal_O1.27mm_Z10.0mm; LCSC# C7470718
D6, D7, D8, D9, D11: WS2812E-1313; LCSC C5446700
D10: WS2812E-1313
F1: 0.75A; Fuse_0603_1608Metric; LCSC# C182438
J1: Battery; BAT-TH_BH-AAA-A1AJ024; LCSC# C5290193
J2: Add_On; PinSocket_2x03_P2.54mm_Vertical; LCSC# C5116527
J4: e-paper; FPC-Epaper; LCSC# C19273954
JP1: Jumper_3_Open; SolderJumper-3_P1.3mm_Bridged12_Pad1.0x1.5mm; not fitted
L1: 47uH; L_Taiyo-Yuden_MD-4040; LCSC# C7588678
P1: USB_C_Plug_USB2.0; C393939; LCSC# C393939
Q1: DMG3415U-7; SOT-23; LCSC# C96616
Q2: NX3008NBK; SOT-23; LCSC# C179399
Q3: AO3402; SOT-23; LCSC# C2874692
R1: 22R; R_0603_1608Metric; LCSC# C313710
R2: 100K; R_0603_1608Metric; LCSC# C25803
R3, R4: 5k1; R_0603_1608Metric; LCSC# C113390
R5: 2.2R; R_0603_1608Metric; LCSC# C2086340
R6, R8, R13: 10K; R_0603_1608Metric; LCSC# C2930027
R7, R10: 4.7K; C_0603_1608Metric; LCSC# C2907166
R9: 100R; R_0603_1608Metric; LCSC# C122970
R11: 470R; R_0603_1608Metric
R12: 330R; R_0603_1608Metric; LCSC# C705847
SW1: ON; MSK12C02; LCSC# C431540
SW2, SW3, SW4, SW5, SW6, SW7, SW8, SW9: SW_SPST_TL3342; LCSC# C318889
U1: TSOP34436; Vishay_MINICAST-3Pin; LCSC# C6561171
U2: XC6220B331MR-G; SOT-23-5; LCSC# C86534
U4: ESP32-S3-MINI-1; ESP32-S2-MINI-1; LCSC# C2913206
U10: LIS2DH; LGA-14_2x2mm_P0.35mm_LayoutBorder3x4y; LCSC# C155670

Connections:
+3V3: C2.1, C3.1, C4.1, C5.1, C24.1, C25.1, C26.1, C27.1, C32.2, C37.1, D6.1 (VDD), D7.1 (VDD), D8.1 (VDD), D9.1 (VDD), D10.1 (VDD), D11.1 (VDD), J2.1, JP1.1 (A), R6.2, R7.1, R9.1, R10.1, R12.1, U2.5 (VOUT), U4.3 (3V3), U10.7 (Vdd_IO), U10.8 (Vdd)
+BATT: J1.2, Q1.3 (D)
/A: C22.2, SW8.2, U4.16 (IO12)
/B: C23.2, SW9.2, U4.15 (IO11)
/BOOT: C6.2, SW2.2, U4.4 (IO0)
/BUSY: J4.16, U4.8 (IO4)
/CS#: J4.13, U4.5 (IO1)
/D+: P1.A6 (D+), U4.24 (USB_D+)
/D-: P1.A7 (D-), U4.23 (USB_D-)
/DOWN: C14.2, SW7.2, U4.12 (IO8)
/D/C#: J4.14, U4.6 (IO2)
/EN: C7.2, R6.1, SW3.2, U4.45 (EN)
/GDR: J4.23, Q2.1 (G), R8.2
/INT1: U4.10 (IO6), U10.6 (INT1)
/IR_IN: U1.1 (OUT), U4.21 (IO17)
/IR_OUT: R1.1, U4.22 (IO18)
/LEFT: C12.2, SW5.2, U4.13 (IO9)
/NEO: R11.1, U4.25 (IO21)
/RES#: J4.15, U4.17 (IO13)
/RESE: J4.22, Q2.2 (S), R5.2
/RIGHT: C13.2, SW6.2, U4.14 (IO10)
/SCL: J2.4, J4.12, R7.2, U4.20 (IO16), U10.1 (SCL/SPC)
/SDA: J2.3, J4.11, R10.2, U4.19 (IO15), U10.2 (SDA/SDI)
/TSCL: J4.19
/TSDA: J4.18
/UP: C11.2, SW4.2, U4.11 (IO7)
/VCI: C15.1, C16.2, J4.9, J4.10, JP1.2 (C), L1.2
/VCOM: C21.2, J4.1
/VDD: C17.2, J4.7
/VGH: C8.2, D4.1 (K), J4.4
/VGL: C9.1, D3.2 (A), J4.2
/VHDR: C19.2, J4.20
/VSH: C18.2, J4.5
/VSL: C20.2, J4.3
/ePaper_on: JP1.3 (B), U4.9 (IO5)
GND: C1.2, C2.2, C3.2, C4.2, C5.2, C6.1, C7.1, C8.1, C9.2, C11.1, C12.1, C13.1, C14.1, C15.2, C16.1, C17.1, C18.1, C19.1, C20.1, C21.1, C22.1, C23.1, C24.2, C25.2, C26.2, C27.2, C32.1, C37.2, D2.1 (K), D6.3 (VSS), D7.3 (VSS), D8.3 (VSS), D9.3 (VSS), D10.3 (VSS), D11.3 (VSS), J1.1, J2.2, J4.8, J4.17, J4.MP (MountPin), P1.A1 (GND), P1.A12 (GND), P1.B1 (GND), P1.B12 (GND), P1.S1 (SHIELD), Q3.3 (S), R2.2, R3.1, R4.1, R5.1, R8.1, R13.1, SW2.1, SW3.1, SW4.1, SW5.1, SW6.1, SW7.1, SW8.1, SW9.1, U1.2 (GND), U2.2 (GND), U4.1 (GND), U4.2 (GND), U4.42 (GND), U4.43 (GND), U4.46 (GND), U4.47 (GND), U4.48 (GND), U4.49 (GND), U4.50 (GND), U4.51 (GND), U4.52 (GND), U4.53 (GND), U4.54 (GND), U4.55 (GND), U4.56 (GND), U4.57 (GND), U4.58 (GND), U4.59 (GND), U4.60 (GND), U4.61 (GND), U4.62 (GND), U4.63 (GND), U4.64 (GND), U4.65 (GND), U10.9 (GND), U10.10 (GND), U10.11 (GND), U10.12 (GND), U10.13 (GND), U10.14 (GND)
unnamed: D1.1 (K), Q1.2 (S), SW1.2 (B)
unnamed: C10.1, D2.2 (A), D3.1 (K)
unnamed: C10.2, D4.2 (A), L1.1, Q2.3 (D)
unnamed: D5.2 (A), R12.2
unnamed: D5.1 (K), Q3.1 (D)
unnamed: D6.4 (DIN), R11.2
unnamed: D6.2 (DOUT), D7.4 (DIN)
unnamed: D7.2 (DOUT), D8.4 (DIN)
unnamed: D8.2 (DOUT), D9.4 (DIN)
unnamed: D9.2 (DOUT), D10.4 (DIN)
unnamed: D10.2 (DOUT), D11.4 (DIN)
unnamed: F1.1, P1.A4 (VBUS), P1.A9 (VBUS), P1.B4 (VBUS), P1.B9 (VBUS)
unnamed: P1.A5 (CC), R3.2
unnamed: P1.B5 (VCONN), R4.2
unnamed: Q3.2 (G), R1.2, R13.2
unnamed: C1.1, SW1.3 (A), U2.1 (VIN), U2.3 (EN)
unnamed: R9.2, U1.3 (Vs)
VBUS: D1.2 (A), F1.2, Q1.1 (G), R2.1

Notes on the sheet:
INFRARED
BUTTONS
MCU
USB-C
POWER-SUPPLY-SELECTOR
ACCELEROMETER
SAO
NEOPIXEL
E-PAPER-SCREEN

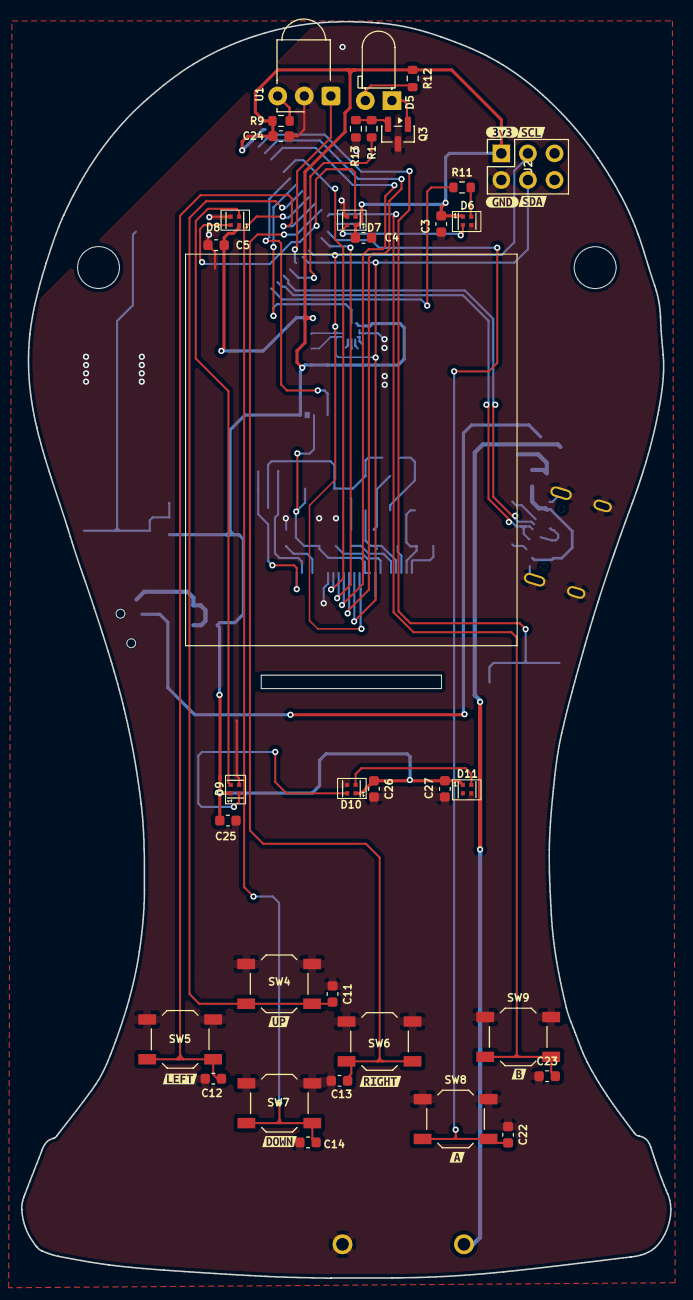
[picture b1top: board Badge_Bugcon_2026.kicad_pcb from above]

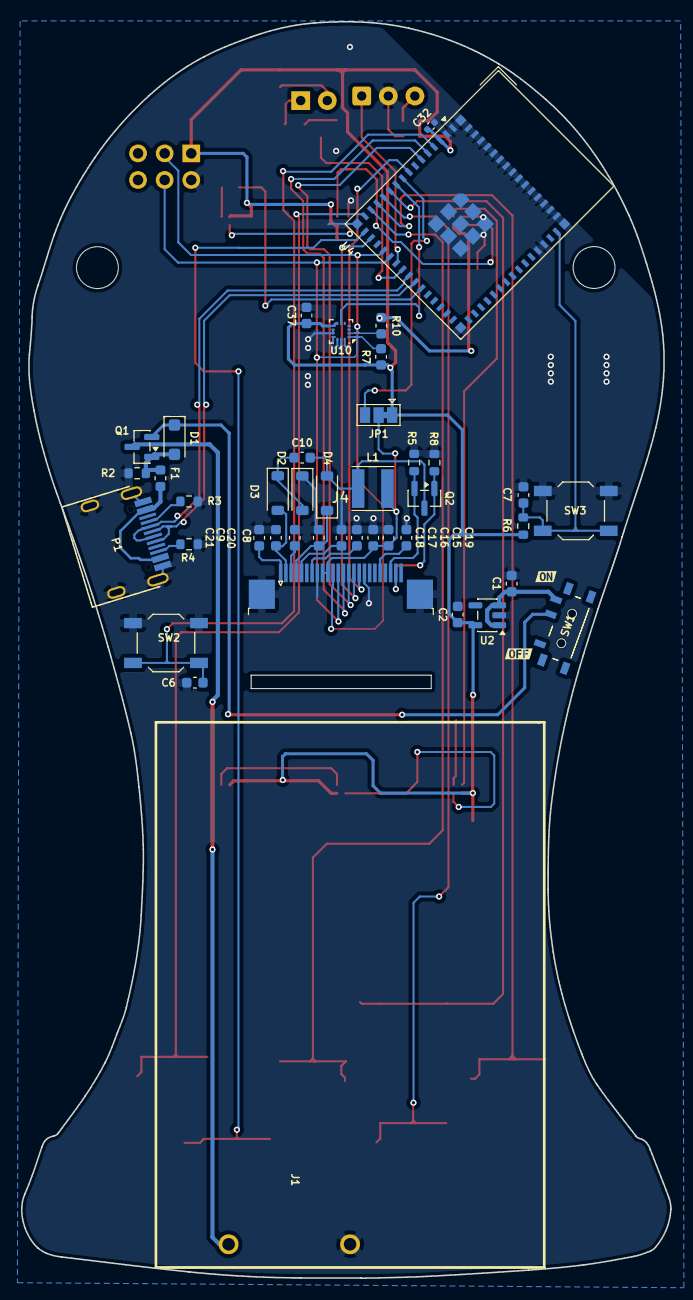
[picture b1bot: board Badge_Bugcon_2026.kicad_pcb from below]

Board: 2 copper layers, 62.0 x 120.0 mm, 88 parts (44 on the bottom side), 52 nets.

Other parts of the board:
kibuzzard-6A986E0D: G***; kibuzzard-6A986E0D
kibuzzard-6A986E2F: G***; kibuzzard-6A986E2F
kibuzzard-6A986E5F: G***; kibuzzard-6A986E5F
kibuzzard-6A986E50: G***; kibuzzard-6A986E50
kibuzzard-6A986EAC: G***; kibuzzard-6A986EAC
kibuzzard-6A986ED3: G***; kibuzzard-6A986ED3
kibuzzard-6A986EE3: G***; kibuzzard-6A986EE3
kibuzzard-6A986F27: G***; kibuzzard-6A986F27
kibuzzard-6A986F32: G***; kibuzzard-6A986F32
kibuzzard-6A986F44: G***; kibuzzard-6A986F44
kibuzzard-6A9897AE: G***; kibuzzard-6A9897AE
kibuzzard-6A98978A: G***; kibuzzard-6A98978A
